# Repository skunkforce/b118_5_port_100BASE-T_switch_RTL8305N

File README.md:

# edgy_board number b118
This design is part of the [edgy board project](https://github.com/skunkforce/edgy_boards). It provides a cheap 5 port 100BASE-T switch.

# getting started
This repository uses submodules. After cloning use the command 

```$ git submodule update --init --recursive```

to pull the submodules before opening the project with kicad. 

# Tests
Tests can be found in [TESTS.md](TESTS.md)

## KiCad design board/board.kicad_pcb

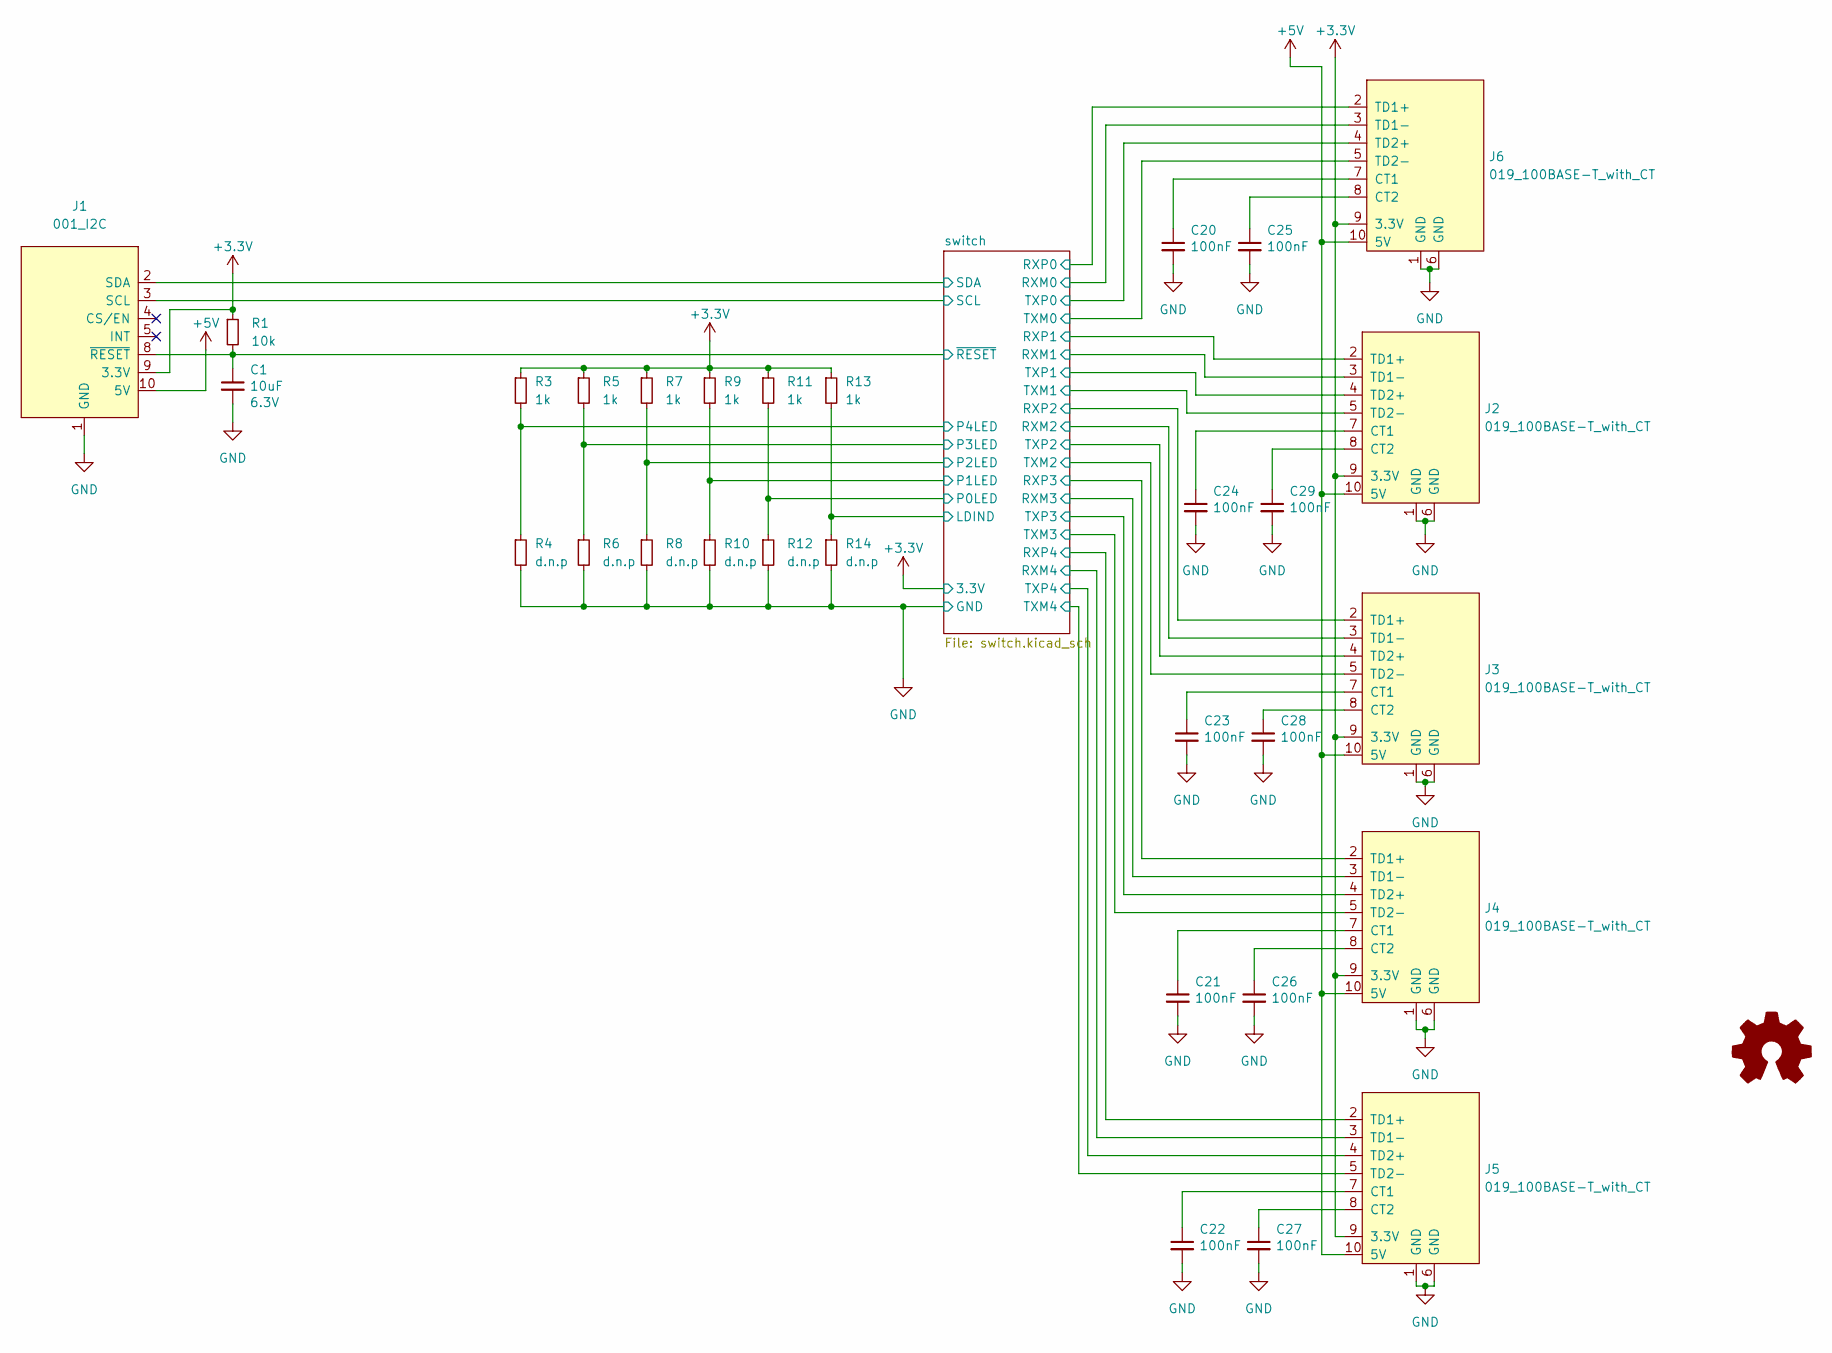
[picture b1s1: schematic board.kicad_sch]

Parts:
C1: 10uF; C_0402_1005Metric; Voltage 6.3V; MPN CL05A105MP5NNNC; Digi-Key_PN 1276-1448-1-ND
C20, C21, C22, C23, C24, C25, C26, C27, C28, C29: 100nF; C_0603_1608Metric
J1: 001_I2C; on_edge_2x05_device
J2, J3, J4, J5, J6: 019_100BASE-T_with_CT; on_edge_2x05_host
LOGO1: Logo_Open_Hardware_Small; OSHW-Symbol_6.7x6mm_SilkScreen
R1: 10k; R_0603_1608Metric
R3, R5, R7, R9, R11, R13: 1k; R_0603_1608Metric
R4, R6, R8, R10, R12, R14: d.n.p; R_0402_1005Metric

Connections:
+5V: J1.10 (5V), J2.10 (5V), J3.10 (5V), J4.10 (5V), J5.10 (5V), J6.10 (5V)
/switch/LDIND: R13.2, R14.1; also elsewhere on the board
/switch/P0LED: R11.2, R12.1; also elsewhere on the board
/switch/P1LED: R9.2, R10.1; also elsewhere on the board
/switch/P2LED: R7.2, R8.1; also elsewhere on the board
/switch/P3LED: R5.2, R6.1; also elsewhere on the board
/switch/P4LED: R3.2, R4.1; also elsewhere on the board
/switch/RXM0: J6.3 (TD1-); also elsewhere on the board
/switch/RXM1: J2.3 (TD1-); also elsewhere on the board
/switch/RXM2: J3.3 (TD1-); also elsewhere on the board
/switch/RXM3: J4.3 (TD1-); also elsewhere on the board
/switch/RXM4: J5.3 (TD1-); also elsewhere on the board
/switch/RXP0: J6.2 (TD1+); also elsewhere on the board
/switch/RXP1: J2.2 (TD1+); also elsewhere on the board
/switch/RXP2: J3.2 (TD1+); also elsewhere on the board
/switch/RXP3: J4.2 (TD1+); also elsewhere on the board
/switch/RXP4: J5.2 (TD1+); also elsewhere on the board
/switch/SCL: J1.3 (SCL); also elsewhere on the board
/switch/SDA: J1.2 (SDA); also elsewhere on the board
/switch/TXM0: J6.5 (TD2-); also elsewhere on the board
/switch/TXM1: J2.5 (TD2-); also elsewhere on the board
/switch/TXM2: J3.5 (TD2-); also elsewhere on the board
/switch/TXM3: J4.5 (TD2-); also elsewhere on the board
/switch/TXM4: J5.5 (TD2-); also elsewhere on the board
/switch/TXP0: J6.4 (TD2+); also elsewhere on the board
/switch/TXP1: J2.4 (TD2+); also elsewhere on the board
/switch/TXP2: J3.4 (TD2+); also elsewhere on the board
/switch/TXP3: J4.4 (TD2+); also elsewhere on the board
/switch/TXP4: J5.4 (TD2+); also elsewhere on the board
/switch/~RESET: C1.1, J1.8 (~RESET), R1.2; also elsewhere on the board
GND: C1.2, C20.2, C21.2, C22.2, C23.2, C24.2, C25.2, C26.2, C27.2, C28.2, C29.2, J1.1 (GND), J2.1 (GND), J2.6 (GND), J3.1 (GND), J3.6 (GND), J4.1 (GND), J4.6 (GND), J5.1 (GND), J5.6 (GND), J6.1 (GND), J6.6 (GND), R4.2, R6.2, R8.2, R10.2, R12.2, R14.2; also elsewhere on the board
unnamed: C20.1, J6.7 (CT1)
unnamed: C21.1, J4.7 (CT1)
unnamed: C22.1, J5.7 (CT1)
unnamed: C23.1, J3.7 (CT1)
unnamed: C24.1, J2.7 (CT1)
unnamed: C25.1, J6.8 (CT2)
unnamed: C26.1, J4.8 (CT2)
unnamed: C27.1, J5.8 (CT2)
unnamed: C28.1, J3.8 (CT2)
unnamed: C29.1, J2.8 (CT2)

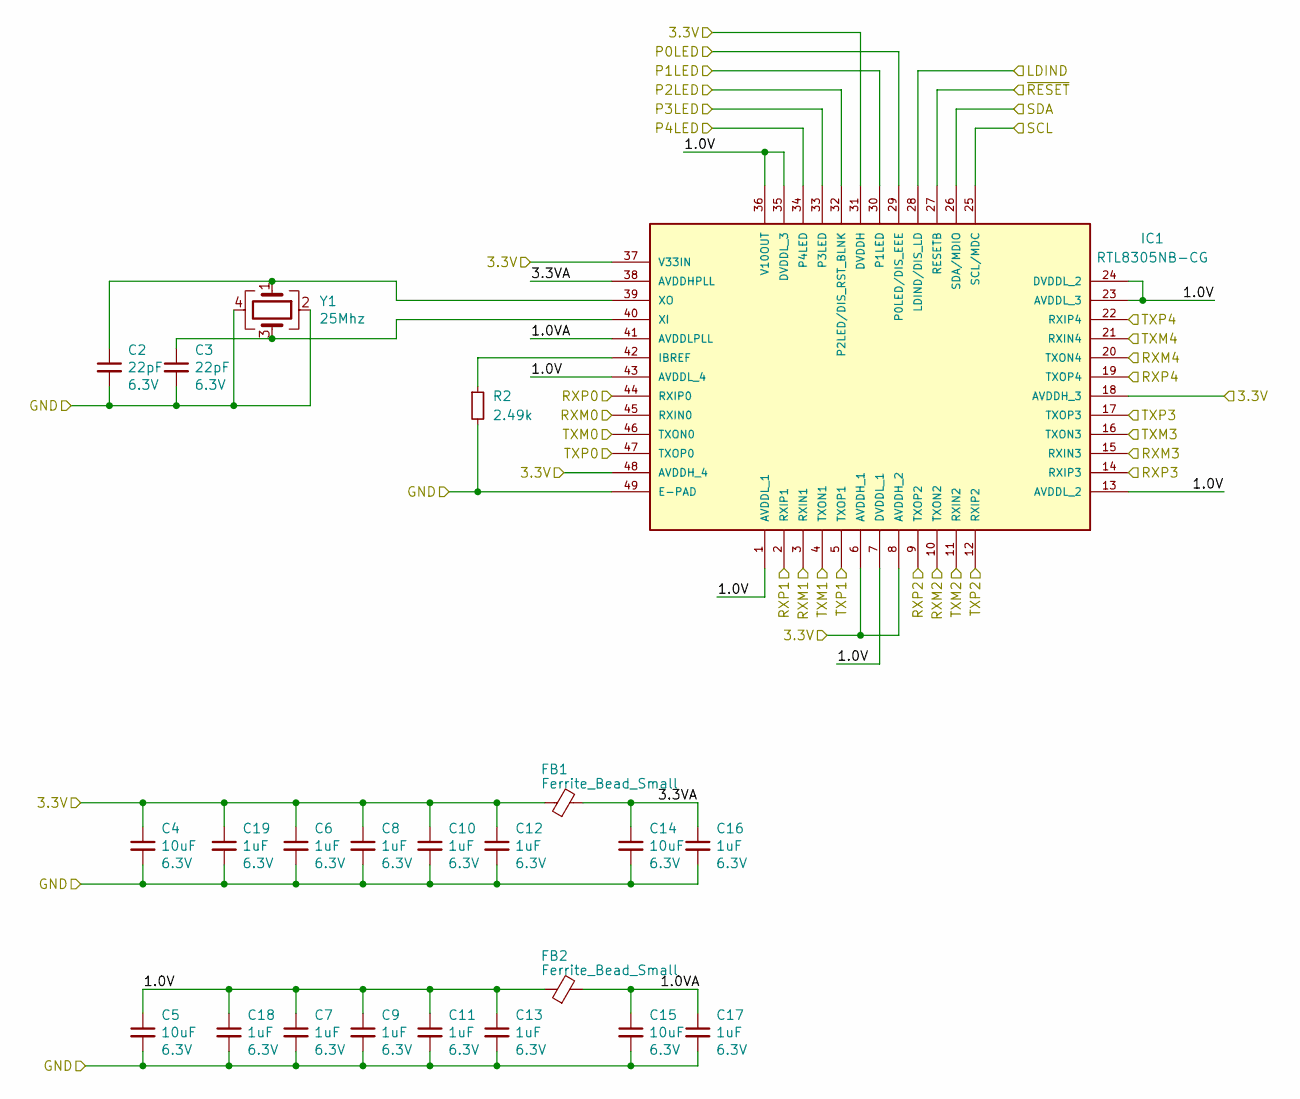
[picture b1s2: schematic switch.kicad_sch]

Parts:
C2, C3: 22pF; C_0402_1005Metric; Voltage 6.3V; Digi-Key_PN 1276-1665-1-ND
C4, C5, C14, C15: 10uF; C_0402_1005Metric; Voltage 6.3V; MPN CL05A105MP5NNNC; Digi-Key_PN 1276-1448-1-ND
C6, C7, C8, C9, C10, C11, C12, C13, C16, C17, C18, C19: 1uF; C_0402_1005Metric; Voltage 6.3V; MPN CL05A105MP5NNNC; Digi-Key_PN 1276-1448-1-ND
FB1, FB2: Ferrite_Bead_Small; L_0603_1608Metric; MPN 74279228111
IC1: RTL8305NB-CG; QFN40PEDITED
R2: 2.49k; R_0603_1608Metric
Y1: 25Mhz; Crystal_SMD_2520-4Pin_2.5x2.0mm; MPN ECS-250-18-36B-CKY-TR

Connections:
/switch/1.0V: C5.1, C7.1, C9.1, C11.1, C13.1, C18.1, FB2.1, IC1.1 (AVDDL_1), IC1.7 (DVDDL_1), IC1.13 (AVDDL_2), IC1.23 (AVDDL_3), IC1.24 (DVDDL_2), IC1.35 (DVDDL_3), IC1.36 (V10OUT), IC1.43 (AVDDL_4)
/switch/1.0VA: C15.1, C17.1, FB2.2, IC1.41 (AVDDLPLL)
/switch/3.3VA: C14.1, C16.1, FB1.2, IC1.38 (AVDDHPLL)
/switch/LDIND: IC1.28 (LDIND/DIS_LD); also elsewhere on the board
/switch/P0LED: IC1.29 (P0LED/DIS_EEE); also elsewhere on the board
/switch/P1LED: IC1.30 (P1LED); also elsewhere on the board
/switch/P2LED: IC1.32 (P2LED/DIS_RST_BLNK); also elsewhere on the board
/switch/P3LED: IC1.33 (P3LED); also elsewhere on the board
/switch/P4LED: IC1.34 (P4LED); also elsewhere on the board
/switch/RXM0: IC1.45 (RXIN0); also elsewhere on the board
/switch/RXM1: IC1.3 (RXIN1); also elsewhere on the board
/switch/RXM2: IC1.10 (TXON2); also elsewhere on the board
/switch/RXM3: IC1.15 (RXIN3); also elsewhere on the board
/switch/RXM4: IC1.20 (TXON4); also elsewhere on the board
/switch/RXP0: IC1.44 (RXIP0); also elsewhere on the board
/switch/RXP1: IC1.2 (RXIP1); also elsewhere on the board
/switch/RXP2: IC1.9 (TXOP2); also elsewhere on the board
/switch/RXP3: IC1.14 (RXIP3); also elsewhere on the board
/switch/RXP4: IC1.19 (TXOP4); also elsewhere on the board
/switch/SCL: IC1.25 (SCL/MDC); also elsewhere on the board
/switch/SDA: IC1.26 (SDA/MDIO); also elsewhere on the board
/switch/TXM0: IC1.46 (TXON0); also elsewhere on the board
/switch/TXM1: IC1.4 (TXON1); also elsewhere on the board
/switch/TXM2: IC1.11 (RXIN2); also elsewhere on the board
/switch/TXM3: IC1.16 (TXON3); also elsewhere on the board
/switch/TXM4: IC1.21 (RXIN4); also elsewhere on the board
/switch/TXP0: IC1.47 (TXOP0); also elsewhere on the board
/switch/TXP1: IC1.5 (TXOP1); also elsewhere on the board
/switch/TXP2: IC1.12 (RXIP2); also elsewhere on the board
/switch/TXP3: IC1.17 (TXOP3); also elsewhere on the board
/switch/TXP4: IC1.22 (RXIP4); also elsewhere on the board
/switch/~RESET: IC1.27 (RESETB); also elsewhere on the board
GND: C2.2, C3.2, C4.2, C5.2, C6.2, C7.2, C8.2, C9.2, C10.2, C11.2, C12.2, C13.2, C14.2, C15.2, C16.2, C17.2, C18.2, C19.2, IC1.49 (E-PAD), R2.2, Y1.2, Y1.4; also elsewhere on the board
unnamed: C2.1, IC1.39 (XO), Y1.1
unnamed: C3.1, IC1.40 (XI), Y1.3
unnamed: IC1.42 (IBREF), R2.1

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
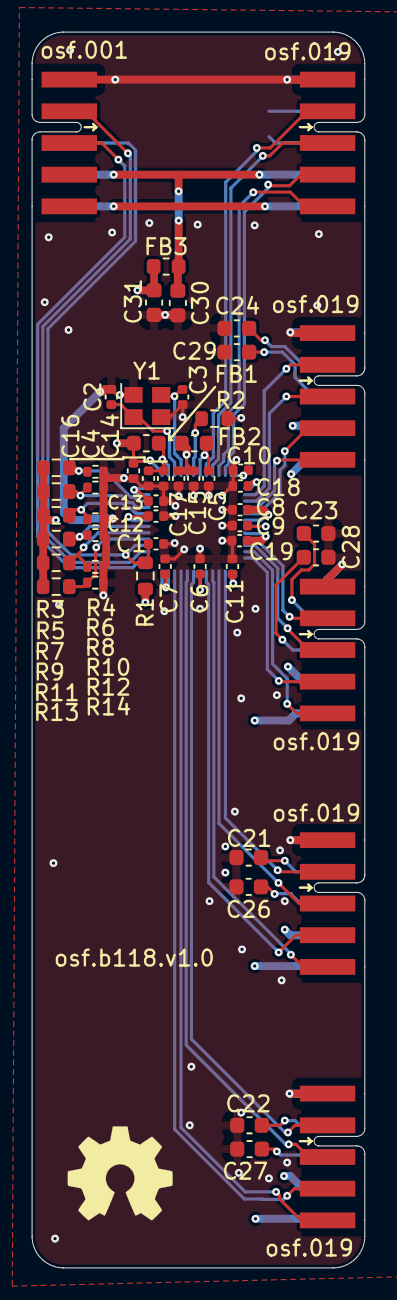
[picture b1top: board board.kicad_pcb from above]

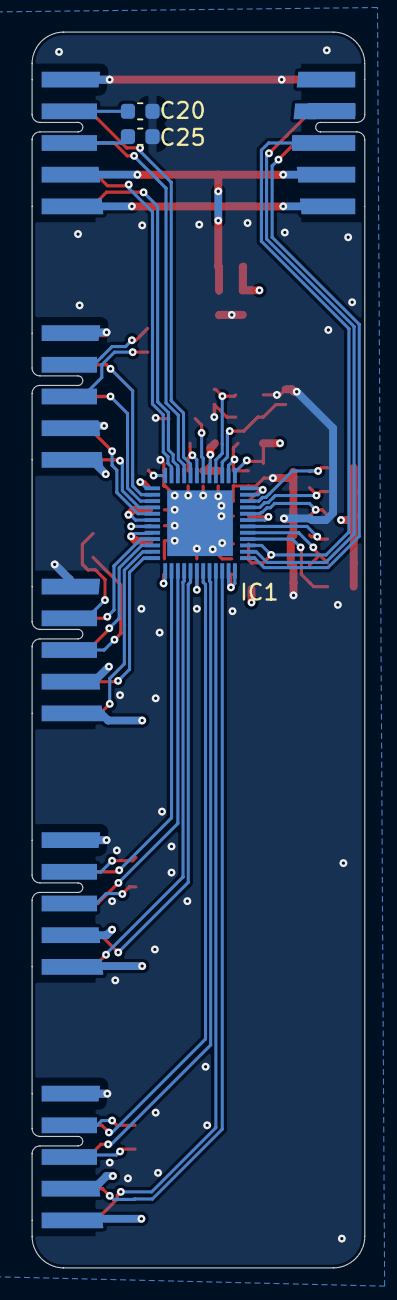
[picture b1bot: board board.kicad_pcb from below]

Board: 4 copper layers, 21.0 x 78.0 mm, 57 parts (3 on the bottom side), 49 nets.

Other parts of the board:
C30, C31: 10uF; C_0603_1608Metric
FB3: 0R; L_0603_1608Metric

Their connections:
GND: C30.2, C31.2; also elsewhere on the board

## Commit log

2023-03-27 initial
2023-03-29 added decoupling
2023-03-30 added N filter for 3.3V input
